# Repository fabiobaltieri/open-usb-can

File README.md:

Open-USB-CAN
============

This project is an USB to CANBus interface based on the ATMega32U2 and an
MCP2515 SPI CANBus controller.

The design features full electrical isolation for the CANBus interface and a
socketcan compliant Linux kernel driver.

> **Warning**
>
> This is not maintained or updated, please check out
> https://github.com/CANnectivity/ or
> https://github.com/candle-usb/candleLight_fw instead.

License
-------

This program is free software: you can redistribute it and/or modify
it under the terms of the GNU General Public License as published by
the Free Software Foundation, either version 3 of the License, or
(at your option) any later version.

Contents
--------

    COPYING        text version of the GPL
    README         this file
    hardware/      source directory for the hardware design files
    firmware/      source directory for the firmware source code
    kernel-module/ source directory for the kernel driver source code

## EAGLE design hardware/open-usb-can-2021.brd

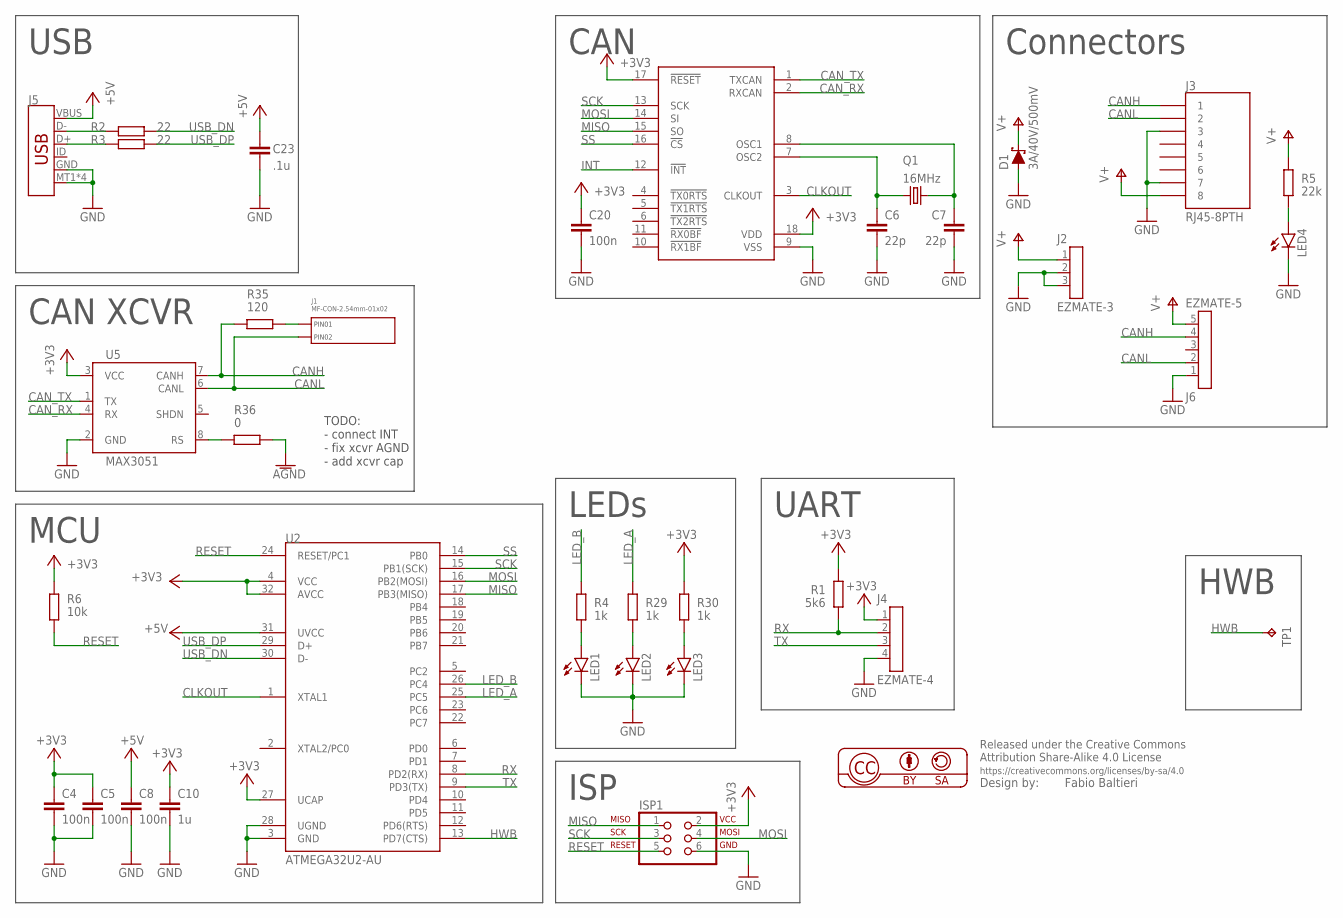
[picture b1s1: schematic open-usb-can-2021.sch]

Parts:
C4, C5, C8, C20: 100n; 0402
C6, C7: 22p; C0805
C10: 1u; 0603
C23: .1u; 0603
D1: 3A/40V/500mV; SMA-DIODE
ISP1: ISP-AVR910TP; 2X03_TP
J1: MF-CON-2.54mm-01x02; PTH_2.54MM_01X02
J2: EZMATE-3
J3: RJ45-8PTH; RJ45-8
J4: EZMATE-4
J5: USB_MICRO-B_SMT; USB-MICROB
J6: EZMATE-5
LED1, LED2, LED3, LED4: LEDCHIPLED_0603; CHIPLED_0603
Q1: 16MHz; HC49U-V
R1: 5k6; 0402
R2, R3: 22; 0603
R4, R29, R30: 1k; 0402
R5: 22k; 0603
R6: 10k; 0402
R35: 120; R0805
R36: 0; 0603
TP1: TPTP08R; TP08R
U1: MCP2515-I/P; SO-18DW
U2: ATMEGA32U2-AU; TQFP32-08
U5: MAX3051; SO08

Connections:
+3V3: C4.1, C5.1, C10.1, C20.1, ISP1.2, J4.1, R1.1, R6.1, R30.2, U1.17 (!RESET), U1.18 (VDD), U2.4 (VCC), U2.27 (UCAP), U2.32 (AVCC), U5.3 (VCC)
+5V: C8.1, C23.1, J5.VBUS, U2.31 (UVCC)
AGND: R36.2
CANH: J3.1, J6.4, R35.1, U5.7 (CANH)
CANL: J1.P$2 (PIN2), J3.2, J6.2, U5.6 (CANL)
CAN_RX: U1.2 (RXCAN), U5.4 (RX)
CAN_TX: U1.1 (TXCAN), U5.1 (TX)
CLKOUT: U1.3 (CLKOUT), U2.1 (XTAL1)
GND: C4.2, C5.2, C6.2, C7.2, C8.2, C10.2, C20.2, C23.2, D1.A, ISP1.6, J2.2, J2.3, J3.3, J3.7, J4.4, J5.GND, J5.MT1 (SHIELD), J5.MT2 (SHIELD), J5.P$1 (SHIELD), J5.P$2 (SHIELD), J6.1, LED1.C, LED2.C, LED3.C, LED4.C, U1.9 (VSS), U2.3 (GND), U2.28 (UGND), U5.2 (GND)
HWB: TP1.TP, U2.13 (PD7(CTS))
INT: U1.12 (!INT)
LED_A: R29.2, U2.25 (PC5)
LED_B: R4.2, U2.26 (PC4)
MISO: ISP1.1, U1.15 (SO), U2.17 (PB3(MISO))
MOSI: ISP1.4, U1.14 (SI), U2.16 (PB2(MOSI))
unnamed: J5.D-, R2.1
unnamed: J5.D+, R3.1
unnamed: C7.1, Q1.2, U1.8 (OSC1)
unnamed: C6.1, Q1.1, U1.7 (OSC2)
unnamed: LED4.A, R5.1
unnamed: LED1.A, R4.1
unnamed: LED2.A, R29.1
unnamed: LED3.A, R30.1
unnamed: R36.1, U5.8 (RS)
unnamed: J1.P$1 (PIN1), R35.2
RESET: ISP1.5, R6.2, U2.24 (RESET/PC1)
RX: J4.2, R1.2, U2.8 (PD2(RX))
SCK: ISP1.3, U1.13 (SCK), U2.15 (PB1(SCK))
SS: U1.16 (!CS), U2.14 (PB0)
TX: J4.3, U2.9 (PD3(TX))
USB_DN: R2.2, U2.30 (D-)
USB_DP: R3.2, U2.29 (D+)
V+: D1.C, J2.1, J3.8, J6.5, R5.2

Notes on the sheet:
UART
LEDs
ISP
MCU
USB
CAN
Connectors
CAN XCVR
HWB
TODO: - connect INT - fix xcvr AGND - add xcvr cap

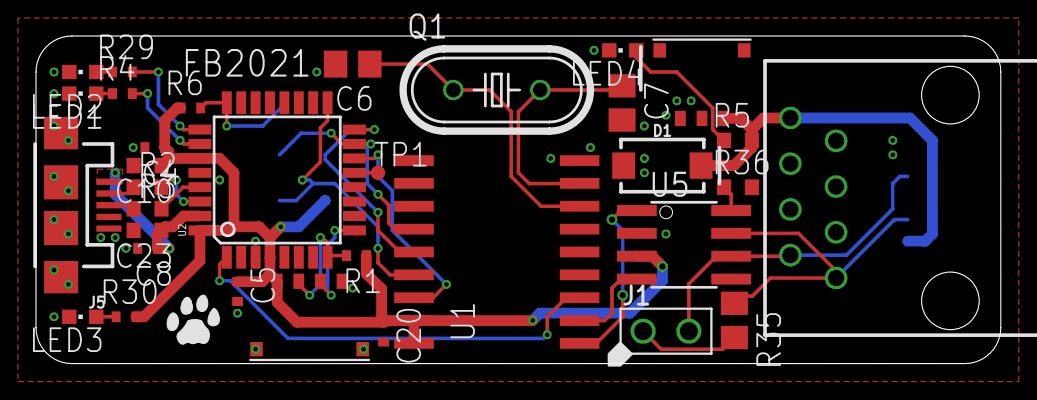
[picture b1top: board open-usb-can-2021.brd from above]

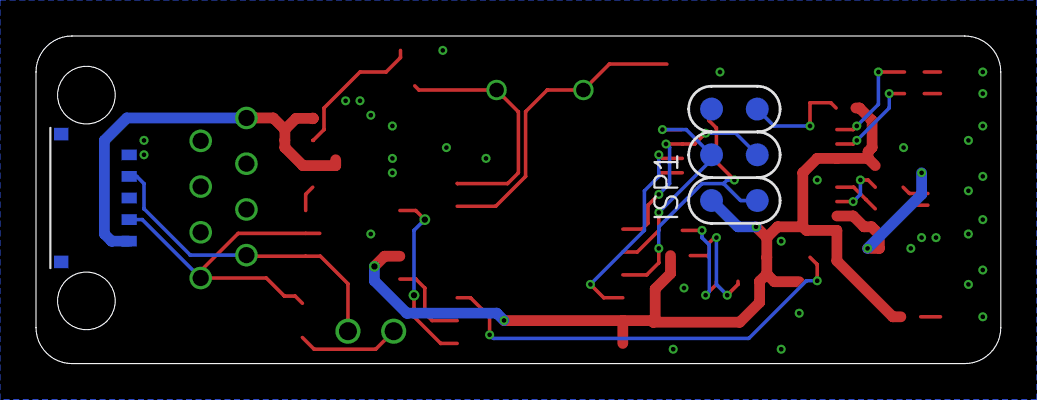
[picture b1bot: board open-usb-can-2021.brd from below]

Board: 4 copper layers, 53.6 x 18.2 mm, 36 parts (2 on the bottom side), 31 nets.

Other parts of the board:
U$1: CAT-L

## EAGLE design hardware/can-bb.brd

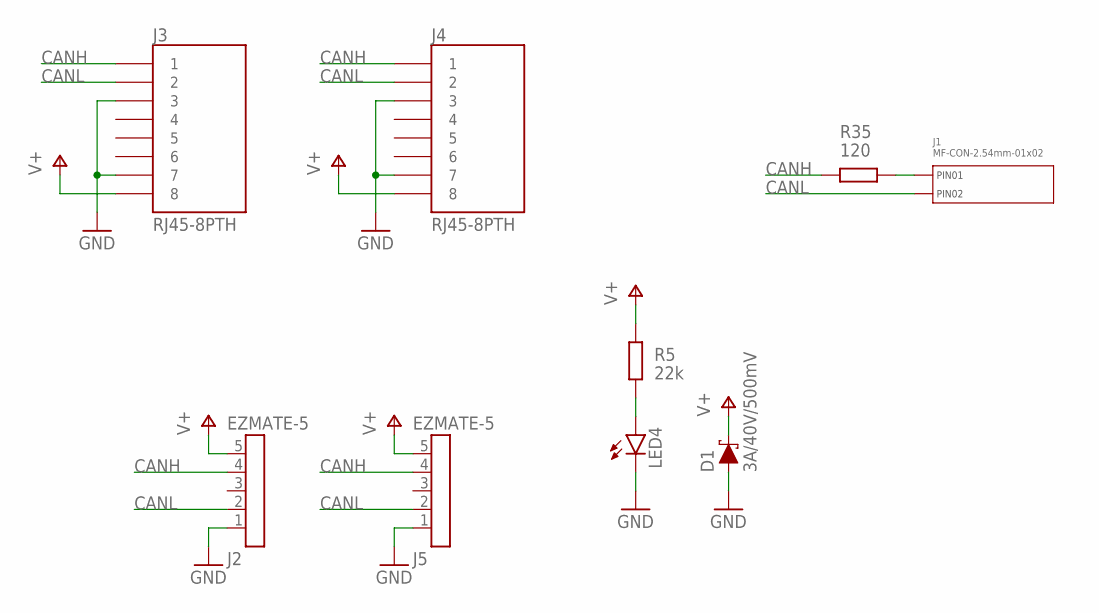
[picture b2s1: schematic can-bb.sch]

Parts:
D1: 3A/40V/500mV; SMA-DIODE
J1: MF-CON-2.54mm-01x02; PTH_2.54MM_01X02
J2, J5: EZMATE-5
J3, J4: RJ45-8PTH; RJ45-8
LED4: LEDCHIPLED_0603; CHIPLED_0603
R5: 22k; 0603
R35: 120; R0805

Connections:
CANH: J2.4, J3.1, J4.1, J5.4, R35.1
CANL: J1.P$2 (PIN2), J2.2, J3.2, J4.2, J5.2
GND: D1.A, J2.1, J3.3, J3.7, J4.3, J4.7, J5.1, LED4.C
unnamed: LED4.A, R5.1
unnamed: J1.P$1 (PIN1), R35.2
V+: D1.C, J2.5, J3.8, J4.8, J5.5, R5.2

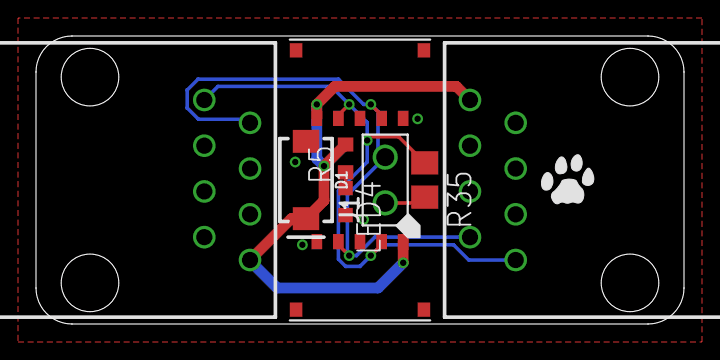
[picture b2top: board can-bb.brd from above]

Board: 4 copper layers, 36.0 x 16.0 mm, 10 parts (0 on the bottom side), 6 nets.

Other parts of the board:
U$1: CAT-L

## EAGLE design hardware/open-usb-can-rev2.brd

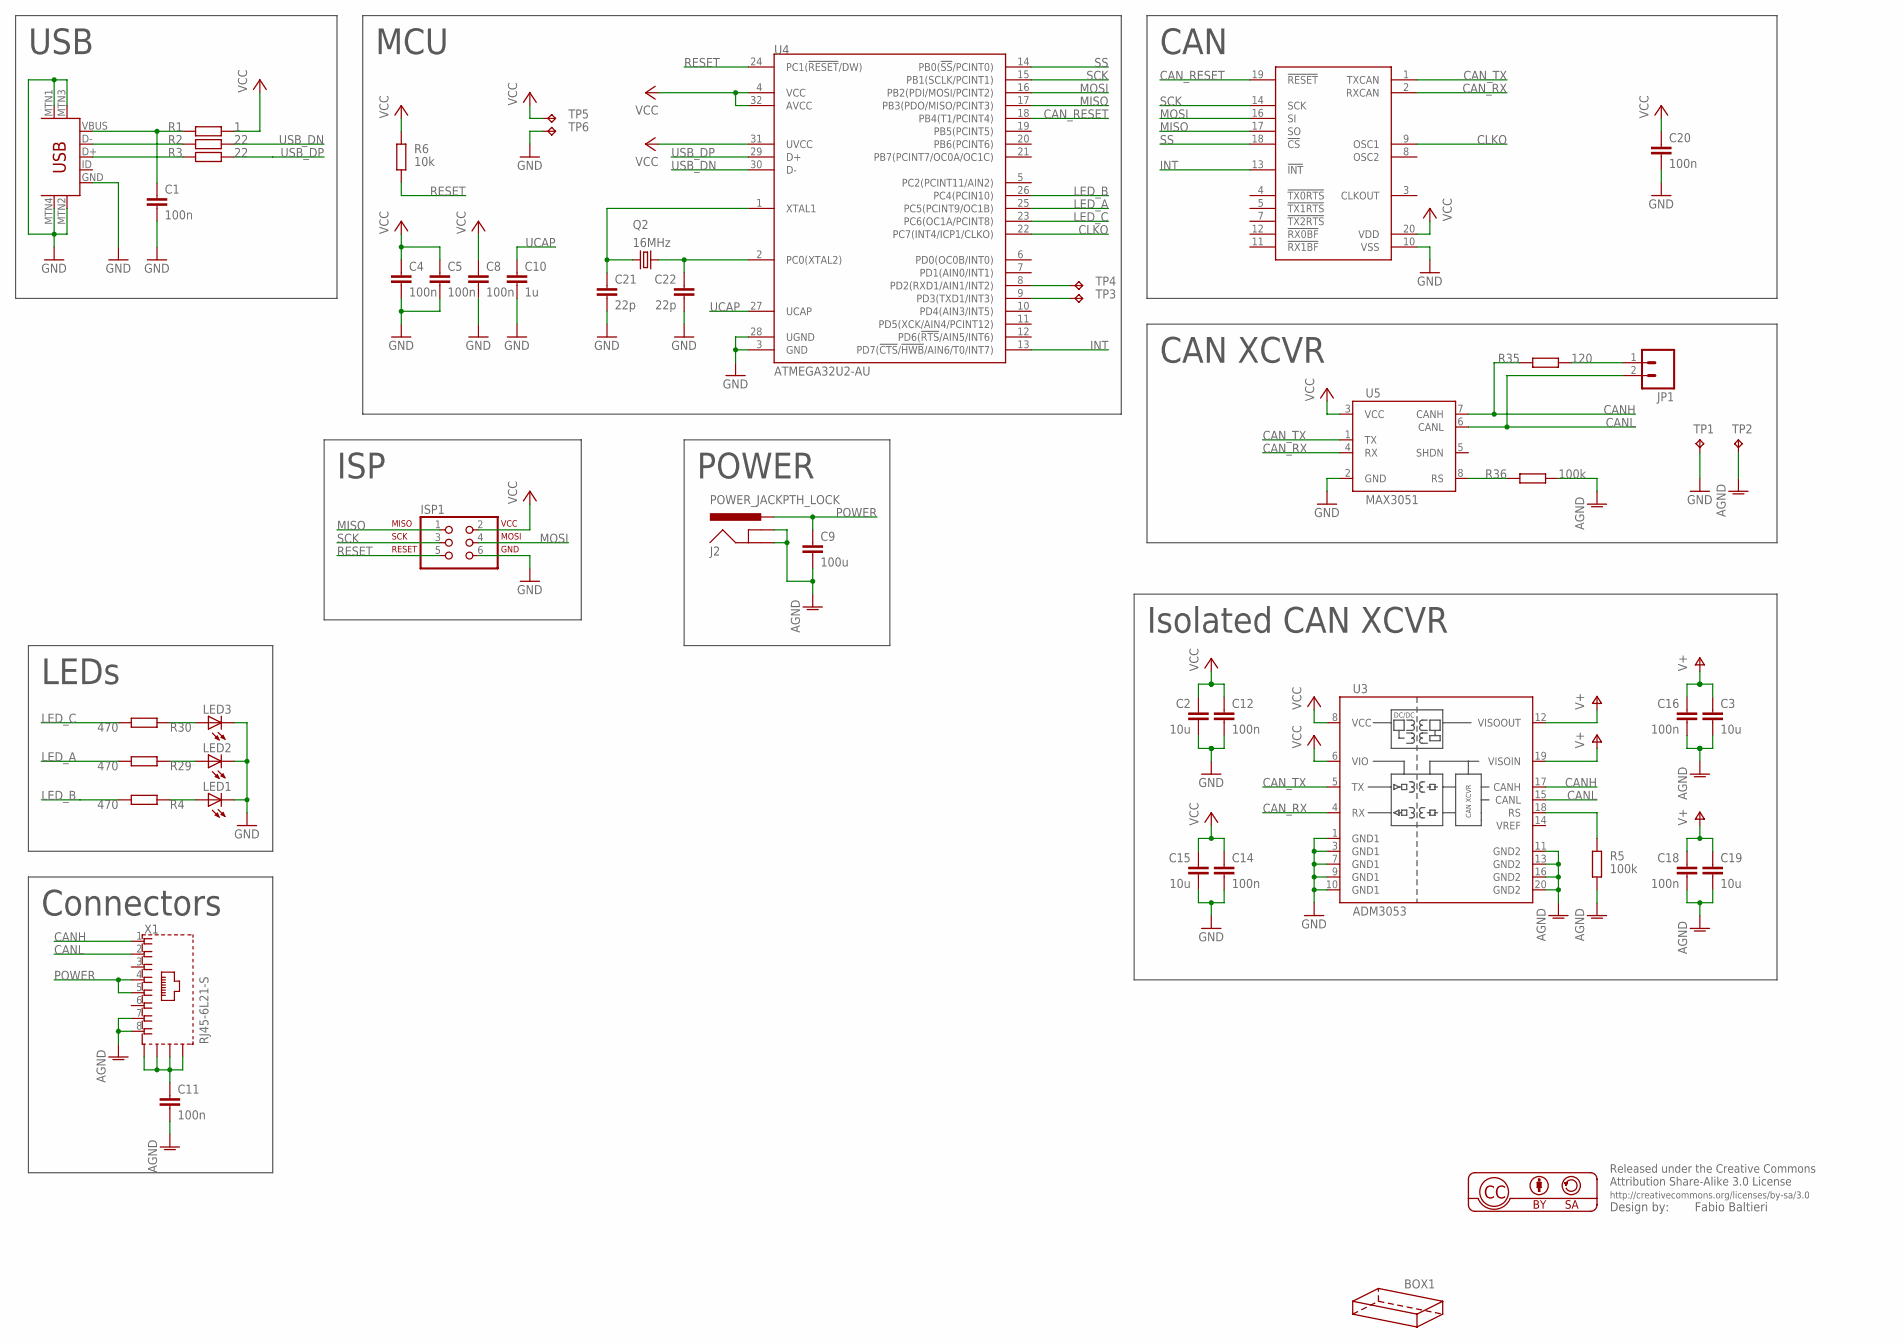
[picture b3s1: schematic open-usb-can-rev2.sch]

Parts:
BOX1: HAMMOND-BOX-R; 1151R
C1, C4, C5, C8, C11, C12, C14, C16, C18, C20: 100n; C0805
C2, C3, C15, C19: 10u; C0805
C9: 100u; C0805
C10: 1u; C0805
C21, C22: 22p; C0805
ISP1: ISP-AVR910PTH; 2X03
J2: POWER_JACKPTH_LOCK; POWER_JACK_PTH_LOCK
JP1: M02PTH; 1X02
LED1, LED2, LED3: LEDCHIPLED_0805; CHIPLED_0805
Q2: 16MHz; CRYSTAL-SMD-5X3
R1: 1; R0603
R2, R3: 22; R0603
R4, R29, R30: 470; R0603
R5, R36: 100k; R0603
R6: 10k; R0603
R35: 120; R0805
TP1, TP2: TPTP16SQ; TP16SQ
TP3, TP4, TP5, TP6: TPTP11R; TP11R
U1: MCP2515-IST; TSSOP20
U3: ADM3053; SO20W
U4: ATMEGA32U2-AU; TQFP32-08
U5: MAX3051; SO08
U$2: USB-MINIB-5PIN; USB-MINIB
X1: RJ45-6L21-S; RJ45-SHIELD1

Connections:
AGND: C3.2, C9.2, C11.2, C16.2, C18.2, C19.2, J2.GND, J2.GNDBREAK, R5.2, R36.2, TP2.TP, U3.11 (GND2), U3.13 (GND2), U3.16 (GND2), U3.20 (GND2), X1.7, X1.8
CANH: R35.1, U3.17 (CANH), U5.7 (CANH), X1.1
CANL: JP1.2, U3.15 (CANL), U5.6 (CANL), X1.2
CAN_RESET: U1.19 (!RESET), U4.18 (PB4(T1/PCINT4))
CAN_RX: U1.2 (RXCAN), U3.4 (RX), U5.4 (RX)
CAN_TX: U1.1 (TXCAN), U3.5 (TX), U5.1 (TX)
CLKO: U1.9 (OSC1), U4.22 (PC7(INT4/ICP1/CLKO))
GND: C1.2, C2.2, C4.2, C5.2, C8.2, C10.2, C12.2, C14.2, C15.2, C20.2, C21.2, C22.2, ISP1.6, LED1.C, LED2.C, LED3.C, TP1.TP, TP6.TP, U1.10 (VSS), U3.1 (GND1), U3.3 (GND1), U3.7 (GND1), U3.9 (GND1), U3.10 (GND1), U4.3 (GND), U4.28 (UGND), U5.2 (GND), U$2.GND, U$2.MTN1 (MTN2), U$2.MTN2 (MTN3), U$2.MTN3 (MTN1), U$2.MTN4
INT: U1.13 (!INT), U4.13 (PD7(!CTS!/!HWB!/AIN6/T0/INT7))
LED_A: R29.2, U4.25 (PC5(PCINT9/OC1B))
LED_B: R4.2, U4.26 (PC4(PCIN10))
LED_C: R30.2, U4.23 (PC6(OC1A/PCINT8))
MISO: ISP1.1, U1.17 (SO), U4.17 (PB3(PDO/MISO/PCINT3))
MOSI: ISP1.4, U1.16 (SI), U4.16 (PB2(PDI/MOSI/PCINT2))
unnamed: C1.1, R1.1, U$2.VBUS
unnamed: R2.1, U$2.D-
unnamed: R3.1, U$2.D+
unnamed: C21.1, Q2.1, U4.1 (XTAL1)
unnamed: C22.1, Q2.3 (2), U4.2 (PC0(XTAL2))
unnamed: LED1.A, R4.1
unnamed: C11.1, X1.S1 (S), X1.S2 (S), X1.S3 (S), X1.S4 (S)
unnamed: R5.1, U3.18 (RS)
unnamed: LED2.A, R29.1
unnamed: LED3.A, R30.1
unnamed: R36.1, U5.8 (RS)
unnamed: JP1.1, R35.2
POWER: C9.1, J2.PWR, X1.4, X1.5
RESET: ISP1.5, R6.2, U4.24 (PC1(!RESET!/DW))
RX: TP4.TP, U4.8 (PD2(RXD1/AIN1/INT2))
SCK: ISP1.3, U1.14 (SCK), U4.15 (PB1(SCLK/PCINT1))
SS: U1.18 (!CS), U4.14 (PB0(!SS!/PCINT0))
TX: TP3.TP, U4.9 (PD3(TXD1/INT3))
UCAP: C10.1, U4.27 (UCAP)
USB_DN: R2.2, U4.30 (D-)
USB_DP: R3.2, U4.29 (D+)
V+: C3.1, C16.1, C18.1, C19.1, U3.12 (VISOOUT), U3.19 (VISOIN)
VCC: C2.1, C4.1, C5.1, C8.1, C12.1, C14.1, C15.1, C20.1, ISP1.2, R1.2, R6.1, TP5.TP, U1.20 (VDD), U3.6 (VIO), U3.8 (VCC), U4.4 (VCC), U4.31 (UVCC), U4.32 (AVCC), U5.3 (VCC)

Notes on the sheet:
LEDs
ISP
MCU
USB
POWER
CAN
Connectors
CAN XCVR
Isolated CAN XCVR

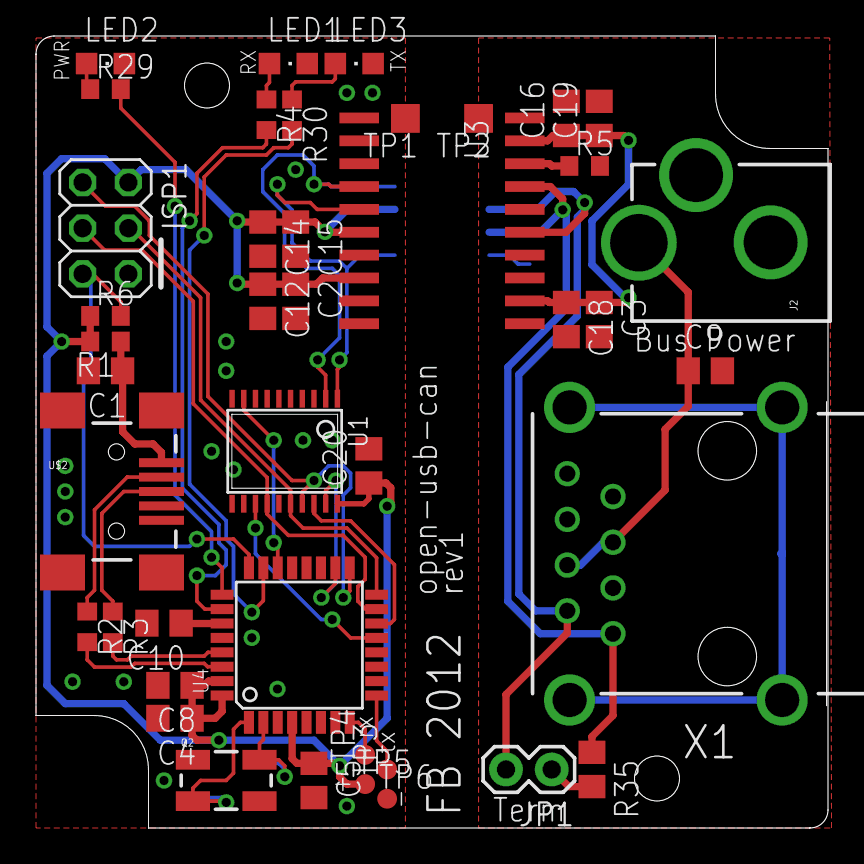
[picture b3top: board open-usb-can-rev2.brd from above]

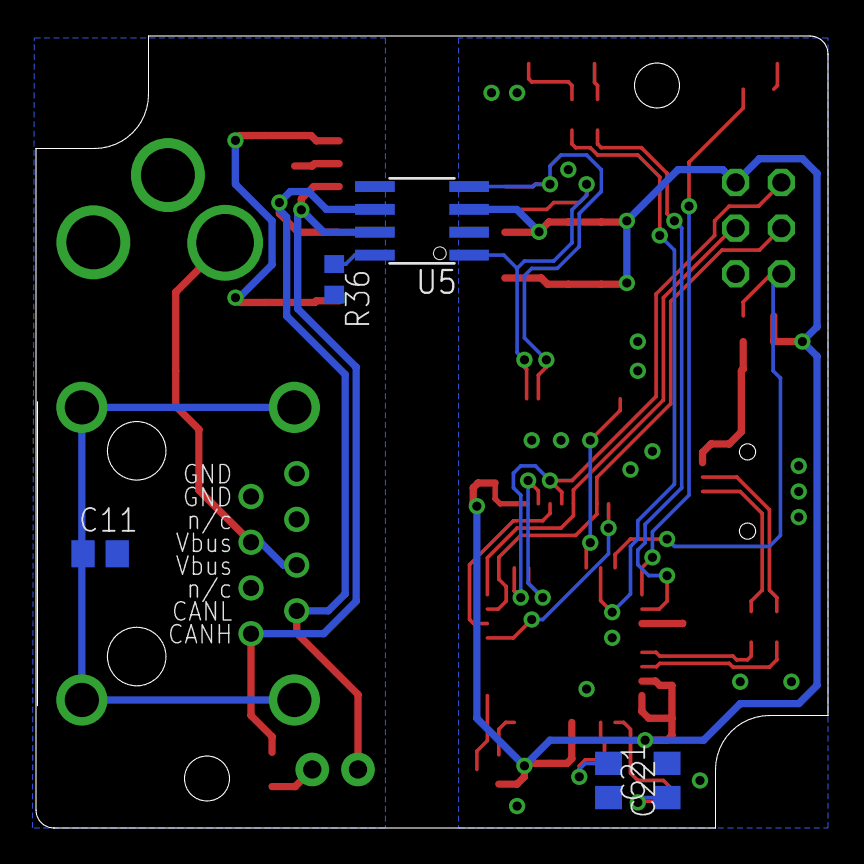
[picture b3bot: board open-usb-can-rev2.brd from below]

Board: 2 copper layers, 44.0 x 44.0 mm, 48 parts (5 on the bottom side), 37 nets.

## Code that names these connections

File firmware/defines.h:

/* buttons */
#define BUTTON_PORT PORTD
#define BUTTON_DDR  DDRD
#define BUTTON_PIN  PIND
#define BUTTON_HWB PC7

#define condition_init() { BUTTON_PORT |= _BV(BUTTON_HWB); }
#define button_read() (BUTTON_PIN & _BV(BUTTON_HWB))

/* leds */
#define LED_A_PORT PORTC
#define LED_A_DDR  DDRC
#define LED_A PC5
#define LED_B_PORT PORTC
#define LED_B_DDR DDRC
#define LED_B PC4

#define led_init() { LED_A_DDR |= _BV(LED_A); LED_B_DDR |= _BV(LED_B); }

#define led_a_on()     LED_A_PORT |=  _BV(LED_A)
#define led_a_off()    LED_A_PORT &= ~_BV(LED_A)
#define led_a_toggle() LED_A_PORT ^=  _BV(LED_A)
#define led_b_on()     LED_B_PORT |=  _BV(LED_B)
#define led_b_off()    LED_B_PORT &= ~_BV(LED_B)
#define led_b_toggle() LED_B_PORT ^=  _BV(LED_B)

/* CAN SPI */
#define SPI_DDR  DDRB
#define SPI_PORT PORTB
#define SPI_SS   PB0
#define SPI_SCK  PB1
#define SPI_MOSI PB2
#define SPI_MISO PB3

#define can_cs_h() (SPI_PORT |=  _BV(SPI_SS))
#define can_cs_l() (SPI_PORT &= ~_BV(SPI_SS))

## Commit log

2011-10-15 README: add empty readme file
2011-10-15 hardware: add hardware files
2011-10-15 kernel-module: initial import of ems driver
2011-10-16 firmware: initial commit based on qi code
2011-10-16 firmware: add ep1 out
2011-10-16 minor cleanups and style changes
2011-10-16 make EP_SIZE defines
2011-10-16 add product and manufacturer descriptions
2011-10-16 move string descriptors to descr.c
2011-10-16 .gitignore: add gitignore file
2011-10-16 descr: cleanup string structures, remove sernum
2011-10-16 move NUM_EPS define out of board.h file
2011-10-16 board: minor cleanups
2011-10-16 minor style cleanups
2011-10-16 rename atusb to main
2011-10-16 main: move led_init in a separate function
2011-10-16 descr: change USB ids
2011-10-16 add canbus structures
2011-10-16 rename to open-usb-can
2011-10-16 hardware: rename open-can-usb to open-usb-can
2011-10-16 kernel-module: first build
2011-10-16 kernel-module: skip alternative interfaces
2011-10-16 kernel-module: add EILSEQ to return check list on rx cb
2011-10-16 firmware: code for testing builk in endpoint
2011-10-16 kernel-module: support multiple can packets per usb frame
2011-10-16 kernel-module: change urb buffers counts
2011-10-22 Makefile: change MCU to atmega32u2
2011-10-22 defines.h: fix pin mapping for open-usb-can board
2011-10-22 spi, mcp2515: add original drivers
2011-10-22 add mcp2515 initialization
2011-10-22 kernel-module: correct usb data structures
2011-10-22 mcp2515: correct intendation, add txempty function
2011-10-22 firmware: add buffer code
2011-10-22 firmware: fix buffer define mistype
2011-10-22 reworked free slots notification logic
2011-10-22 buffer: rise to 32 packets
2011-10-22 main: change blink sequence
2011-10-23 usb: change ep sizes
2011-10-23 mcp2515: export read and write register function
2011-10-23 spi: start with chip select high
2011-10-23 main: add delay before first spi command
2011-10-23 ep0: implement basic ep0 functionalities
2011-10-23 descr: remove misleading id comments
2011-10-24 kernel-module: add hw version information and ep0 protocol
2011-10-24 kernel-module: add bus configuration support
2011-10-24 firmware: add bus configuration support
2011-10-24 kernel-module: support start/stop control commands
2011-10-24 buffer: reenable hw and style fixes
2011-10-24 mcp2515: implement bus configuration
2011-10-25 mcp2515: better CTRL register handling
2011-10-25 buffer: add barriers around mcp/spi functions
2011-10-25 kernel-module: fix clock.freq for mcp2515 chip
2011-10-25 firmware: add led blink support
2011-10-25 kernel-module and firmware: add one-shot mode support
2011-10-25 ep0: call buffer_reset before mcp2515_start
2011-10-26 buffer: move tx_buf_w++ into tx buffer callback
2011-10-26 kernel-module: add tx and rx debug printks
2011-10-26 kernel-module: reworked stop_queue/wake_queue logic
2011-10-26 firmware: use read status command on mcp2515
2011-10-26 kernel-module: add some headroom with queue management
2011-10-26 mcp2515: clear tx buffer on stop
2011-10-26 buffer: fix reset function
    Without this fix the controller send a wrong packet after a buffer_reset
    as the usb buffer is already preapred to the old tx_buf_w.
2011-10-26 ep0: reset buffers also on stop
2011-11-02 handle /2 fixed clock divisor in firmware instead of kernel
2011-11-12 mcp2515: add write_bits function
2011-11-12 mcp2515: reworked status flags logic
2011-11-12 firmware: add 16MHz F_CPU option (for 5V boards)
2011-11-12 mcp2515.c: one-shot txbuf_empty walkaround
    ...to be further investigated
2011-11-12 firmware: implement can error handling
2011-11-12 Revert "handle /2 fixed clock divisor in firmware instead of kernel"
    This reverts commit 69abf564cfaf4b9aebedb0c5fbea37409a8667a1 as it was
    causing problems with canbus at maximum frequency.
2011-11-20 COPYING: add license information
2011-11-20 firmware: update copyright information
2011-11-20 kernel-module: update copyright information
2011-11-20 hardware: add CC BY-SA license
2012-02-27 firmware: atu2: change usb TX acknowledge sequence
    This one works with double-banked endpoints.
2012-02-27 firmware: usb: add EPF_TRUNCATE support
2012-03-05 kernel-module: convert to use module_usb_driver()
2012-03-11 firmware: aut2: add TRUNCATE flag for data EPs
2012-04-22 kernel-module: indentation fixes
2012-04-23 kernel-module: change most messages to netdev_* functions
2012-04-23 kernel-module: remove unused defines
2012-04-23 firmware: fix indentation style
2012-04-23 firmware: change declared consumption to 100mA
2012-08-28 Makefile: default F_CPU to 16MHz
2012-08-28 hw: add pdf schematics
2012-08-28 bootloader: add dfu bootloader sources
2012-08-28 kernel-module: minor fixes
2012-08-29 bootloader: change vendor name
2012-08-29 fw: change vendor/product string
2012-08-29 bootloader: new Makefile
2012-08-29 bootloader: add .gitignore file
2012-08-29 fw: new Makefile
2012-08-29 fw: add dep files to .gitignore
2012-08-29 hw: add .gitignore file
2012-08-29 kernel-module: .gitignore improvements
2012-08-29 bootloader: make bootloader timeout-based
2012-08-31 Makefile: remove redundant -Os
2012-09-02 bootloader: fix vendor indentation style
2012-09-05 use USB ID assigned from openmoko pool
    Use the two product IDs assigned from the open projects pool of Openmoko
    vendor ID.
    Thanks to FIC, Openmoko and Harald Welte.
2012-09-07 hw: clean up, update to eagle 6
2012-09-16 fw: Makefile: add device ID to dfu-util
2012-09-16 fw: mcp2515: do not reread status in rx function
2012-09-16 fw: mcp2515: use only buffer 0 (as it was anyway)
2012-09-16 fw: buffer: cleanup rx_process code
2012-09-16 fw: Makefile: compile in -O3
2012-09-16 fw: buffer: remove some unnecessary volatile
2012-11-13 hw: add rev2 rc0
2012-11-27 fw: Makefile: remove -R from DFU_UTIL_FLAGS
2012-12-14 kernel-module: update to last kernel module code
2013-01-16 kernel-module: update to latest version
2013-06-10 Add README file
2013-12-02 kernel-module: remove LED references for old kernels
2015-04-08 kernel-module: use the module build link for kernel sources
2020-05-17 kernel-module: use netif_trans_update
2021-02-27 README: empty, drop
2021-10-12 hw: add 2021 board and can-bb
2021-10-12 hw: drop rev2, never built
2021-10-29 hw: 2021: add few notes
2021-10-29 hw: 2021: fix a couple of schematic warnings
2022-03-15 kernel-module: update the echo skb apis
2022-12-23 README: add a pointer to candleLight_fw
2024-08-28 README: add a link to CANnectivity

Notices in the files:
parts and their libraries:
SparkFun-DiscreteSemi: Licensing: Creative Commons ShareAlike 4.0 International - https://creativecommons.org/licenses/by-sa/4.0
SparkFun-Connectors: Licensing: CC v3.0 Share-Alike You are welcome to use this library for commercial purposes.
balto: Released under the Creative Commons
